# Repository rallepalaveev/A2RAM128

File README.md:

# A2RAM128

This is an expansion 128kB RAM card for Apple2 computers, which uses the the upper 16kB, which are mapped to the 12kB ROM space $D000-$FFFF.

The card uses the standard 50-pin slots, and adds 8 banks of 16kB - a total of 128kB, based on modern chips like SRAM, and not needing to have any additional cables to connect to the motherboard.

This project is based on one 128kB SRAM chip and one PLD for logic.

The logic of the card follows the design recommendations of the Saturn cards:

There are 8 x 16kB banks of the following organization:
* Two sub-banks A and B of 4kB are mapped to $D000-$DFFF
* One sub-bank of 8kB is mapped to $E000-$FFFF

Bank-switched RAM soft switches:

| Address | Symbolic Name | Bank | Read From | Write to RAM? |
|:--------|:--------------|:-----|:----------|:--------------|
|$C0N0|READBSR2|2|RAM|No|
|$C0N1|WRITEBSR2|2|ROM|Yes*|
|$C0N2|OFFBSR2|2|ROM|No|
|$C0N3|RDWRBSR2|2|RAM|Yes*|
|$C0N8|READBSR1|1|RAM|No|
|$C0N9|WRITEBSR1|1|ROM|Yes*|
|$C0NA|OFFBSR1|1|ROM|No|
|$C0NB|RDWRBSR1|1|RAM|Yes*|

| Address | Function |
|:--------|:--------------|
|$C0N4|Select Bank 1|
|$C0N5|Select Bank 2|
|$C0N6|Select Bank 3|
|$C0N7|Select Bank 4|
|$C0NC|Select Bank 5|
|$C0ND|Select Bank 6|
|$C0NE|Select Bank 7|
|$C0NF|Select Bank 8|

N is the Slot Number + 8.

Operation:

The card houses the 3 soft-switches above which upon reset are configured in the default configuration:

* Sub-bank A is selected
* ROM is readable
* RAM is writeable (v2.0 RAM is not writable)

A test to be made for quick check of functionality:

]CALL-151           # Enter monitor

*C0N1               # Start activation of RAM for writing (v2 only)

*C0N1               # Activation of RAM for writing

*F800<F800.FFFFM    # Copy monitor to RAM

*C0N3               # Set RAM for reading

This sequence should not lead to the computer freezing with a responce "$C0N3-", because the monitor is copied to the RAM and continues to work from RAM.

The benefit of the card is that programs which require 64kB of RAM or more can be used - primarily ProDOS. It works from any 50-pin slot with no additional cabling - P&P, however some programs expect that the card is in slot #0, so this is the recommended use.

V2.0 was created to fullfill the requrements by the Saturn cards to activate the card for writing by two succecutive calls to C0N1. It is advisable that this version is used.

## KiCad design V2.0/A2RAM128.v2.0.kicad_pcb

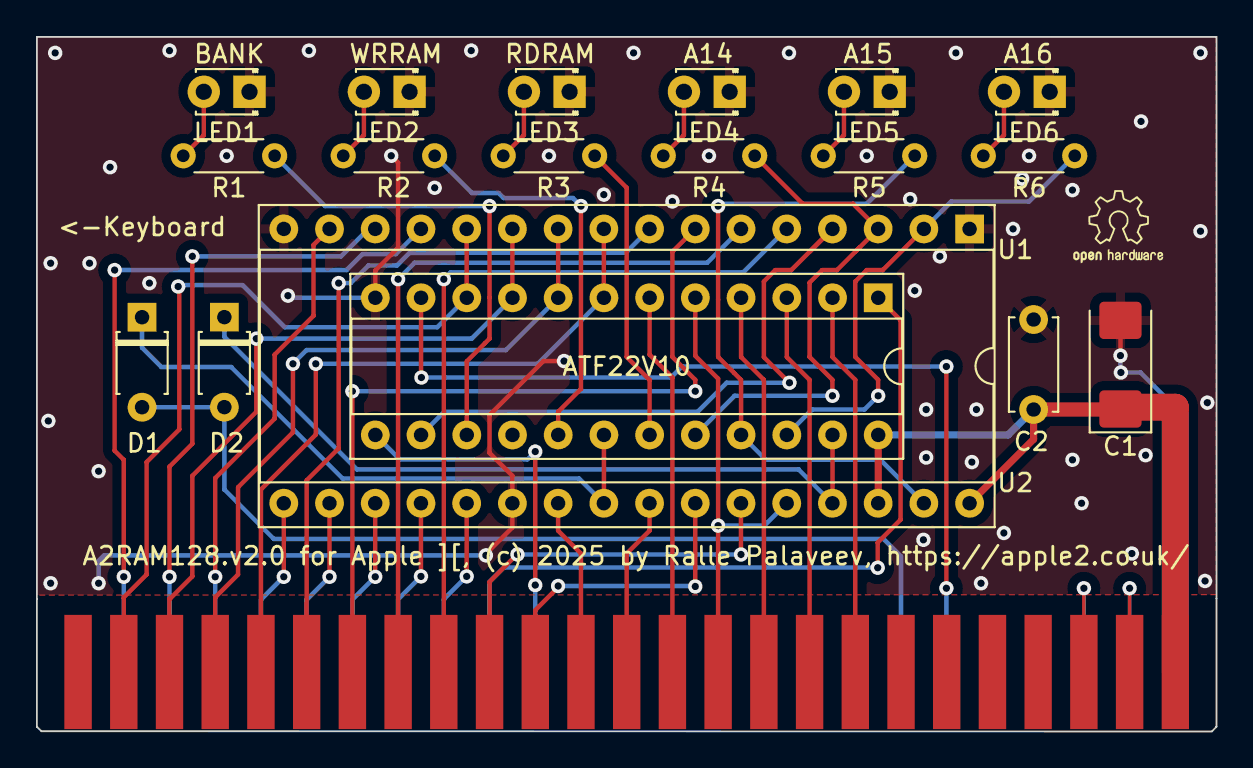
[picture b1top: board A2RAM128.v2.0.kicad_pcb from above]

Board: 2 copper layers, 65.5 x 38.6 mm, 18 parts (0 on the bottom side), 17 nets.

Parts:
C1: 220uF; CP_EIA-6032-15_Kemet-U
C2: 100n; C_Disc_D5.0mm_W2.5mm_P5.00mm
D1, D2: D_T-1_P5.08mm_Horizontal
LED1, LED2, LED3, LED4, LED5, LED6: LED_D1.8mm_W3.3mm_H2.4mm
R1, R2, R3, R4, R5, R6: 1k; R_Axial_DIN0204_L3.6mm_D1.6mm_P5.08mm_Horizontal
U1: DIP-32_W15.24mm_Socket
U2: DIP-24_W7.62mm_Socket

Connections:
5V: C1.1, C2.1, U1.30, U1.32, U2.24
A0: U1.12, U2.10
A1: U1.11, U2.9
A2: U1.10, U2.8
A3: U1.9, U2.7
A13: U1.28, U2.5
BANK: R1.2, U2.15
GND: C1.2, C2.2, LED1.1, LED2.1, LED3.1, LED4.1, LED5.1, LED6.1, U1.1, U1.16, U1.22, U2.12
INH: D1.2, D2.2
OE: D1.1, U1.24, U2.18
RA12: U1.4, U2.14
RA14: R4.2, U1.3, U2.20
RA15: R5.2, U1.31, U2.21
RA16: R6.2, U1.2, U2.22
RDRAM: R3.2, U2.19
WE: D2.1, U1.29, U2.23
WRRAM: R2.2, U2.17

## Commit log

2024-03-10 Rename A2RAM128.pdf to A2RAM128.sch.pdf

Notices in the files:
V2.0/A2RAM128.v2.0.kicad_pcb:
Hardware design by Ralle Palaveev (c) 2025.
A2RAM128.v2.0 for Apple ][, (c) 2025 by Ralle Palaveev, https://apple2.co.uk
